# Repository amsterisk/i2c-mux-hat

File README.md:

# I2C Mux HAT

An open-hardware 8-channel I2C multiplexer board for single-board computers with a
Raspberry Pi-compatible 40-pin header (Raspberry Pi, Orange Pi, Banana Pi, ...).

Status: **work in progress** — schematic done (ERC clean), PCB routed (DRC clean), not yet reviewed or fabricated.

## Features

- **TCA9548A** 8-channel I2C switch, address 0x70–0x77 (3-way DIP switch, default 0x70).
- **Per-channel voltage**: a 3-pin jumper selects 3.3 V or 5 V for that channel's pull-ups
  and connector power. The mux runs at 3.3 V and translates levels, so 5 V devices never
  reach the host's GPIO.
- **Per-channel connector**: keyed JST XH 4-pin (B4B-XH-A, vertical).
- 2.2 kΩ pull-ups per channel (enabled by a shunt on a 2-pin header), suitable for a few metres of cable.
- Per-channel resettable fuse on connector power and ESD clamp (USBLC6-2SC6) on SDA/SCL/V.
- Optional mux reset from GPIO4 (2-pin header).
- HAT form factor, 65 × 56.5 mm (no ID EEPROM; pins 27/28 unused).
- **2×20 stacking header**: all 40 pins pass through to another board above.

Example use: DDC/CI control of monitors (input switching, brightness) over HDMI's DDC lines,
with one channel per monitor — every monitor answers on the same addresses (0x37/0x50), so
each needs its own bus.

## Connector pinout

JST XH (J*x*01), Grove pin order:

| Pin | Signal |
|---|---|
| 1 | SCL |
| 2 | SDA |
| 3 | V (3.3 or 5 V, per channel jumper) |
| 4 | GND |

### JST XH → HDMI (DDC) cable

| XH pin | HDMI pin |
|---|---|
| 1 SCL | 15 |
| 2 SDA | 16 |
| 3 V | 18 (+5 V) |
| 4 GND | 17 (bridge to 20 / shell) |

Set that channel to **5 V**. Leave all other HDMI pins unconnected.

## Jumpers

| Ref | Default | Function |
|---|---|---|
| JPx01 (1×3 header) | no shunt | Channel x voltage: 1-2 = 3.3 V, 2-3 = 5 V, none = off |
| JPx02 (1×2 header) | shunt fitted | Channel x pull-ups; remove the shunt to disable |
| JP1 (1×2 header) | open | Fit a shunt to connect mux ~RESET to GPIO4 (pin 7) |
| SW1 (DIP-3, 1.27 mm) | all OFF | Address A0–A2; ON = 1, so 0x70 + A (0x70–0x77) |

All jumpers are 2.54 mm pin headers taking standard shunts.

## Stacking

J1 is a 2×20 stacking header (female, long pins through the board), so every GPIO passes
through. A board above can share I2C (pins 3/5) as long as it avoids addresses 0x70–0x77
(or move this board's address with SW1); GPIO4 is only used if JP1 is bridged; pins
27/28 are free for the upper board's ID EEPROM. Mechanically, the vertical XH plugs and
their cables exit upwards, so a board above needs a tall spacer (about 20 mm or more);
otherwise put this board at the top of the stack.

## Software

The board appears as one I2C device (0x70) on the host's bus on pins 3/5.

- **Raspberry Pi OS**: `dtoverlay=i2c-mux,pca9548,addr=0x70` in `config.txt` gives one
  `/dev/i2c-N` per channel. Keep the bus at ≤100 kHz for long cables / DDC
  (`dtparam=i2c_baudrate=100000`); the TCA9548A is rated to 400 kHz.
- **Other boards**: use a device-tree overlay for `i2c-mux-pca954x`, or select channels
  from userspace by writing the channel bitmask to 0x70 before each transaction.

## Building fabrication files

```sh
tools/export.sh            # version from `git describe`; refuses to build if ERC/DRC fail
tools/export.sh v0.1       # explicit version
tools/export.sh --allow-violations   # work-in-progress builds
```

Outputs land in `production/<version>/` (git-ignored; attach to a GitHub release):
Gerber + drill zip (upload as-is to JLCPCB/PCBWay; the stencil is made from `F.Paste`),
grouped BOM, JLCPCB-format BOM + placement file, schematic PDF, top/bottom 3D renders,
and the ERC/DRC reports. Needs KiCad 9 (`kicad-cli`, or `kicad.kicad-cli` from the snap).

Design rules target JLCPCB's standard 2-layer process (Board Setup → Constraints, plus
`hardware/i2c-mux-hat.kicad_dru`): 0.15 mm track/clearance minimum, 0.6/0.3 mm vias,
0.3 mm copper-to-edge. Net classes: *Default* 0.25 mm tracks; *Power* 0.5 mm for
+5V, +3.3V, GND and each channel's VCH/VOUT/VPU.

## Repository layout

- `hardware/` — KiCad 9 project (`i2c-mux-hat.kicad_pro`); the 8 channels are one hierarchical
  sheet (`channel.kicad_sch`) instanced 8 times.
- `tools/export.sh` — builds fabrication and documentation outputs.
- `LICENSE` — CERN-OHL-S-2.0.

## Licence

Copyright the contributors. Licensed under the **CERN Open Hardware Licence Version 2 –
Strongly Reciprocal** (CERN-OHL-S-2.0). See `LICENSE`.

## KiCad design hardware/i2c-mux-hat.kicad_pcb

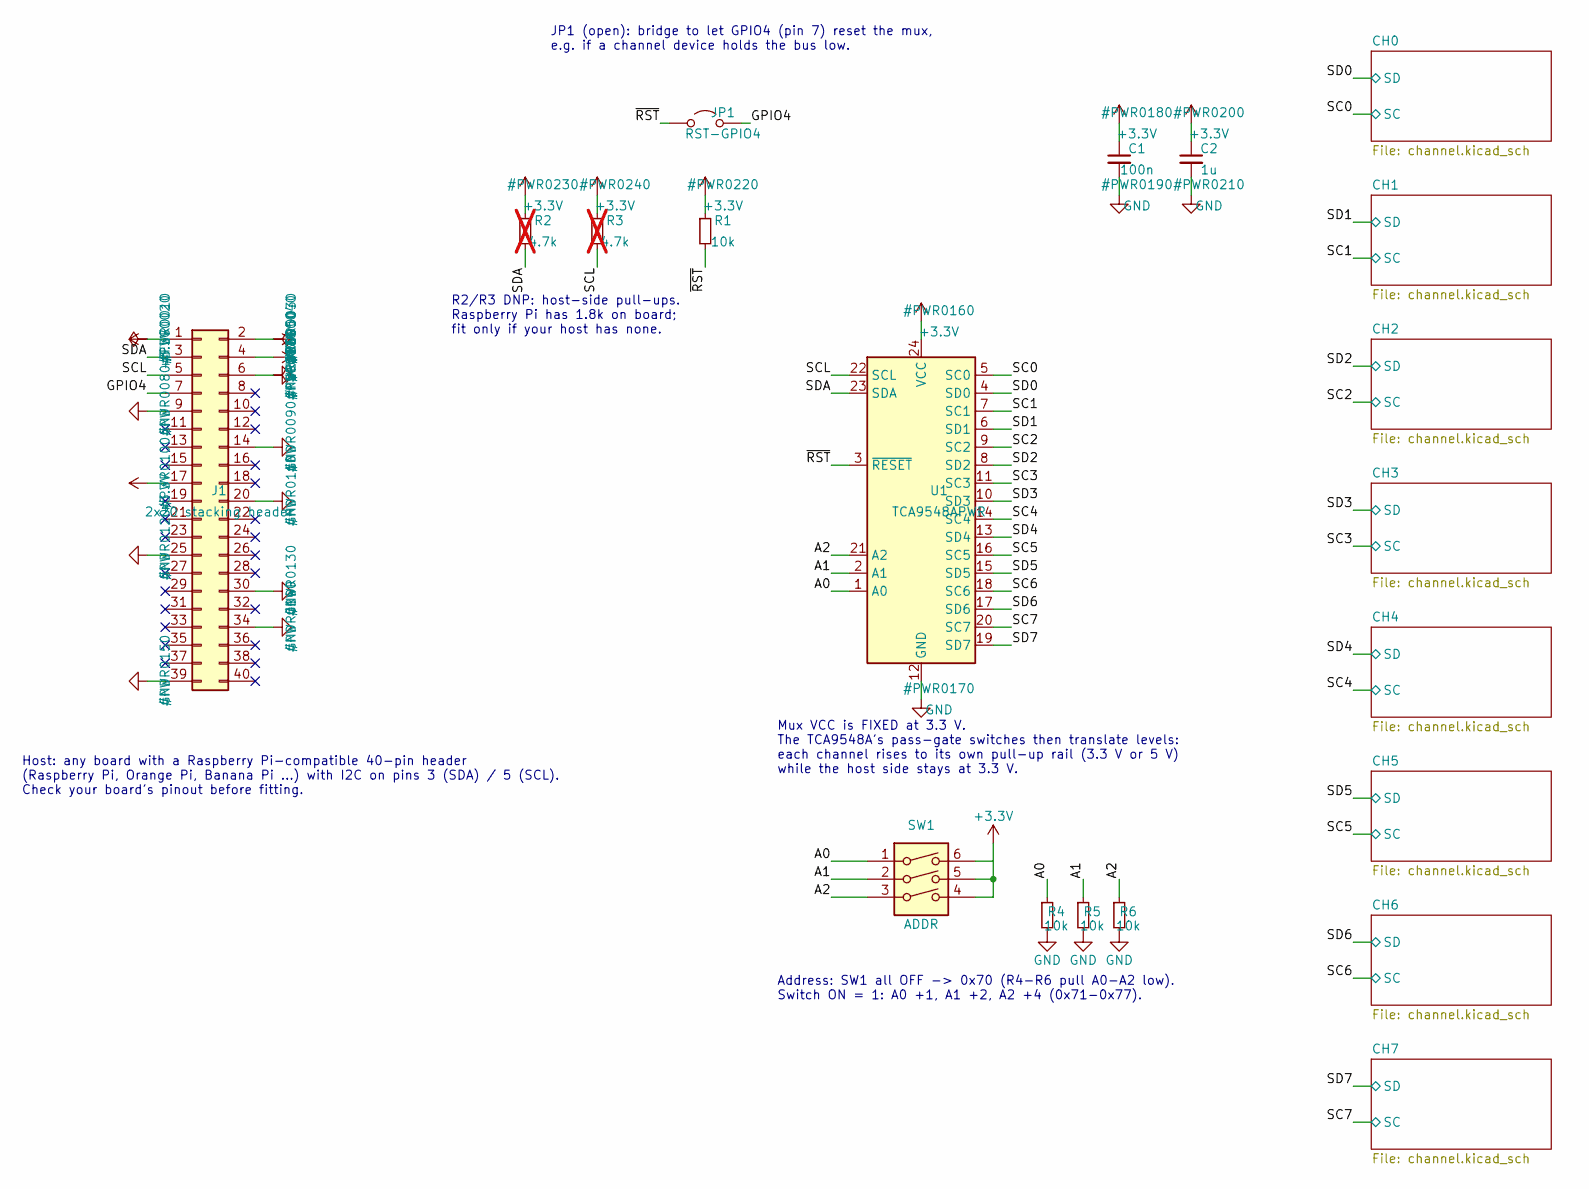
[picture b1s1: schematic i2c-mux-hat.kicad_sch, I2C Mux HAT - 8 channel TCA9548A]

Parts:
C1: 100n; C_0603_1608Metric
C2: 1u; C_0603_1608Metric
J1: 2x20 stacking header; PinSocket_2x20_P2.54mm_Vertical
JP1: RST-GPIO4; PinHeader_1x02_P2.54mm_Vertical
R1, R4, R5, R6: 10k; R_0603_1608Metric
R2, R3: 4.7k; R_0603_1608Metric; not fitted
SW1: ADDR; SW_DIP_SPSTx03_Slide_KingTek_DSHP03TS_W7.62mm_P1.27mm
U1: TCA9548APWR; TSSOP-24_4.4x7.8mm_P0.65mm

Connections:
+3.3V: C1.1, C2.1, J1.1, J1.17, R1.1, R2.1, R3.1, SW1.4, SW1.5, SW1.6, U1.24 (VCC); also elsewhere on the board
+5V: J1.2, J1.4; also elsewhere on the board
/A0: R4.1, SW1.1, U1.1 (A0)
/A1: R5.1, SW1.2, U1.2 (A1)
/A2: R6.1, SW1.3, U1.21 (A2)
/GPIO4: J1.7, JP1.2 (B)
/SC0: U1.5 (SC0); also elsewhere on the board
/SC1: U1.7 (SC1); also elsewhere on the board
/SC2: U1.9 (SC2); also elsewhere on the board
/SC3: U1.11 (SC3); also elsewhere on the board
/SC4: U1.14 (SC4); also elsewhere on the board
/SC5: U1.16 (SC5); also elsewhere on the board
/SC6: U1.18 (SC6); also elsewhere on the board
/SC7: U1.20 (SC7); also elsewhere on the board
/SCL: J1.5, R3.2, U1.22 (SCL)
/SD0: U1.4 (SD0); also elsewhere on the board
/SD1: U1.6 (SD1); also elsewhere on the board
/SD2: U1.8 (SD2); also elsewhere on the board
/SD3: U1.10 (SD3); also elsewhere on the board
/SD4: U1.13 (SD4); also elsewhere on the board
/SD5: U1.15 (SD5); also elsewhere on the board
/SD6: U1.17 (SD6); also elsewhere on the board
/SD7: U1.19 (SD7); also elsewhere on the board
/SDA: J1.3, R2.2, U1.23 (SDA)
/~RST: JP1.1 (A), R1.2, U1.3 (~RESET)
GND: C1.2, C2.2, J1.6, J1.9, J1.14, J1.20, J1.25, J1.30, J1.34, J1.39, R4.2, R5.2, R6.2, U1.12 (GND); also elsewhere on the board

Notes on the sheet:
Address: SW1 all OFF -> 0x70 (R4-R6 pull A0-A2 low). Switch ON = 1: A0 +1, A1 +2, A2 +4 (0x71-0x77).
JP1 (open): bridge to let GPIO4 (pin 7) reset the mux, e.g. if a channel device holds the bus low.
R2/R3 DNP: host-side pull-ups. Raspberry Pi has 1.8k on board; fit only if your host has none.
Host: any board with a Raspberry Pi-compatible 40-pin header (Raspberry Pi, Orange Pi, Banana Pi ...) with I2C on pins 3 (SDA) / 5 (SCL). Check your board's pinout before fitting.
Mux VCC is FIXED at 3.3 V. The TCA9548A's pass-gate switches then translate levels: each channel rises to its own pull-up rail (3.3 V or 5 V) while the host side stays at 3.3 V.

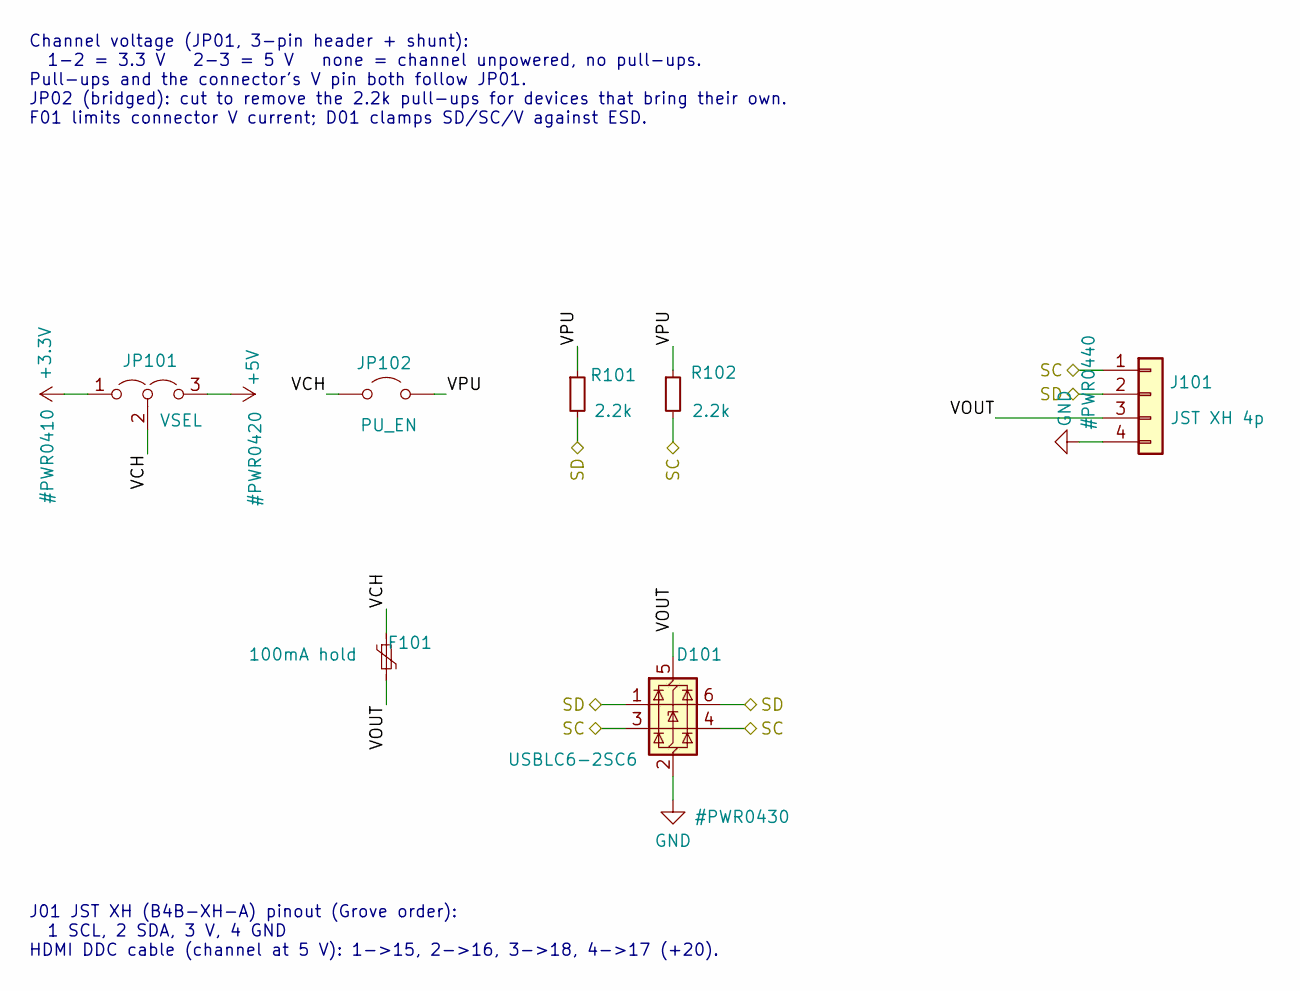
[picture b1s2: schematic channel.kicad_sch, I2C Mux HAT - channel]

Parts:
D101: USBLC6-2SC6; SOT-23-6
F101: 100mA hold; Fuse_0805_2012Metric
J101: JST XH 4p; JST_XH_B4B-XH-A_1x04_P2.50mm_Vertical
JP101: VSEL; PinHeader_1x03_P2.54mm_Vertical
JP102: PU_EN; PinHeader_1x02_P2.54mm_Vertical
R101, R102: 2.2k; R_0603_1608Metric

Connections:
+3.3V: JP101.1 (A); also elsewhere on the board
+5V: JP101.3 (B); also elsewhere on the board
/CH0/VCH: F101.1, JP101.2 (C), JP102.1 (A)
/CH0/VOUT: D101.5 (VBUS), F101.2, J101.3
/CH0/VPU: JP102.2 (B), R101.1, R102.1
/SC0: D101.3 (I/O2), D101.4 (I/O2), J101.1, R102.2; also elsewhere on the board
/SD0: D101.1 (I/O1), D101.6 (I/O1), J101.2, R101.2; also elsewhere on the board
GND: D101.2 (GND), J101.4; also elsewhere on the board

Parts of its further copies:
D201, D301, D401, D501, D601, D701, D801: USBLC6-2SC6; SOT-23-6
F201, F301, F401, F501, F601, F701, F801: 100mA hold; Fuse_0805_2012Metric
J201, J301, J401, J501, J601, J701, J801: JST XH 4p; JST_XH_B4B-XH-A_1x04_P2.50mm_Vertical
JP201, JP301, JP401, JP501, JP601, JP701, JP801: VSEL; PinHeader_1x03_P2.54mm_Vertical
JP202, JP302, JP402, JP502, JP602, JP702, JP802: PU_EN; PinHeader_1x02_P2.54mm_Vertical
R201, R202, R301, R302, R401, R402, R501, R502, R601, R602, R701, R702, R801, R802: 2.2k; R_0603_1608Metric

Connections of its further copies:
+3.3V: JP201.1 (A), JP301.1 (A), JP401.1 (A), JP501.1 (A), JP601.1 (A), JP701.1 (A), JP801.1 (A); also elsewhere on the board
+5V: JP201.3 (B), JP301.3 (B), JP401.3 (B), JP501.3 (B), JP601.3 (B), JP701.3 (B), JP801.3 (B); also elsewhere on the board
/CH1/VCH: F201.1, JP201.2 (C), JP202.1 (A)
/CH1/VOUT: D201.5 (VBUS), F201.2, J201.3
/CH1/VPU: JP202.2 (B), R201.1, R202.1
/CH2/VCH: F301.1, JP301.2 (C), JP302.1 (A)
/CH2/VOUT: D301.5 (VBUS), F301.2, J301.3
/CH2/VPU: JP302.2 (B), R301.1, R302.1
/CH3/VCH: F401.1, JP401.2 (C), JP402.1 (A)
/CH3/VOUT: D401.5 (VBUS), F401.2, J401.3
/CH3/VPU: JP402.2 (B), R401.1, R402.1
/CH4/VCH: F501.1, JP501.2 (C), JP502.1 (A)
/CH4/VOUT: D501.5 (VBUS), F501.2, J501.3
/CH4/VPU: JP502.2 (B), R501.1, R502.1
/CH5/VCH: F601.1, JP601.2 (C), JP602.1 (A)
/CH5/VOUT: D601.5 (VBUS), F601.2, J601.3
/CH5/VPU: JP602.2 (B), R601.1, R602.1
/CH6/VCH: F701.1, JP701.2 (C), JP702.1 (A)
/CH6/VOUT: D701.5 (VBUS), F701.2, J701.3
/CH6/VPU: JP702.2 (B), R701.1, R702.1
/CH7/VCH: F801.1, JP801.2 (C), JP802.1 (A)
/CH7/VOUT: D801.5 (VBUS), F801.2, J801.3
/CH7/VPU: JP802.2 (B), R801.1, R802.1
/SC1: D201.3 (I/O2), D201.4 (I/O2), J201.1, R202.2; also elsewhere on the board
/SC2: D301.3 (I/O2), D301.4 (I/O2), J301.1, R302.2; also elsewhere on the board
/SC3: D401.3 (I/O2), D401.4 (I/O2), J401.1, R402.2; also elsewhere on the board
/SC4: D501.3 (I/O2), D501.4 (I/O2), J501.1, R502.2; also elsewhere on the board
/SC5: D601.3 (I/O2), D601.4 (I/O2), J601.1, R602.2; also elsewhere on the board
/SC6: D701.3 (I/O2), D701.4 (I/O2), J701.1, R702.2; also elsewhere on the board
/SC7: D801.3 (I/O2), D801.4 (I/O2), J801.1, R802.2; also elsewhere on the board
/SD1: D201.1 (I/O1), D201.6 (I/O1), J201.2, R201.2; also elsewhere on the board
/SD2: D301.1 (I/O1), D301.6 (I/O1), J301.2, R301.2; also elsewhere on the board
/SD3: D401.1 (I/O1), D401.6 (I/O1), J401.2, R401.2; also elsewhere on the board
/SD4: D501.1 (I/O1), D501.6 (I/O1), J501.2, R501.2; also elsewhere on the board
/SD5: D601.1 (I/O1), D601.6 (I/O1), J601.2, R601.2; also elsewhere on the board
/SD6: D701.1 (I/O1), D701.6 (I/O1), J701.2, R701.2; also elsewhere on the board
/SD7: D801.1 (I/O1), D801.6 (I/O1), J801.2, R801.2; also elsewhere on the board
GND: D201.2 (GND), D301.2 (GND), D401.2 (GND), D501.2 (GND), D601.2 (GND), D701.2 (GND), D801.2 (GND), J201.4, J301.4, J401.4, J501.4, J601.4, J701.4, J801.4; also elsewhere on the board

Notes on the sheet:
J01 JST XH (B4B-XH-A) pinout (Grove order): 1 SCL, 2 SDA, 3 V, 4 GND HDMI DDC cable (channel at 5 V): 1->15, 2->16, 3->18, 4->17 (+20).
Channel voltage (JP01, 3-pin header + shunt): 1-2 = 3.3 V 2-3 = 5 V none = channel unpowered, no pull-ups. Pull-ups and the connector's V pin both follow JP01. JP02 (bridged): cut to remove the 2.2k pull-ups for devices that bring their own. F01 limits connector V current; D01 clamps SD/SC/V agains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

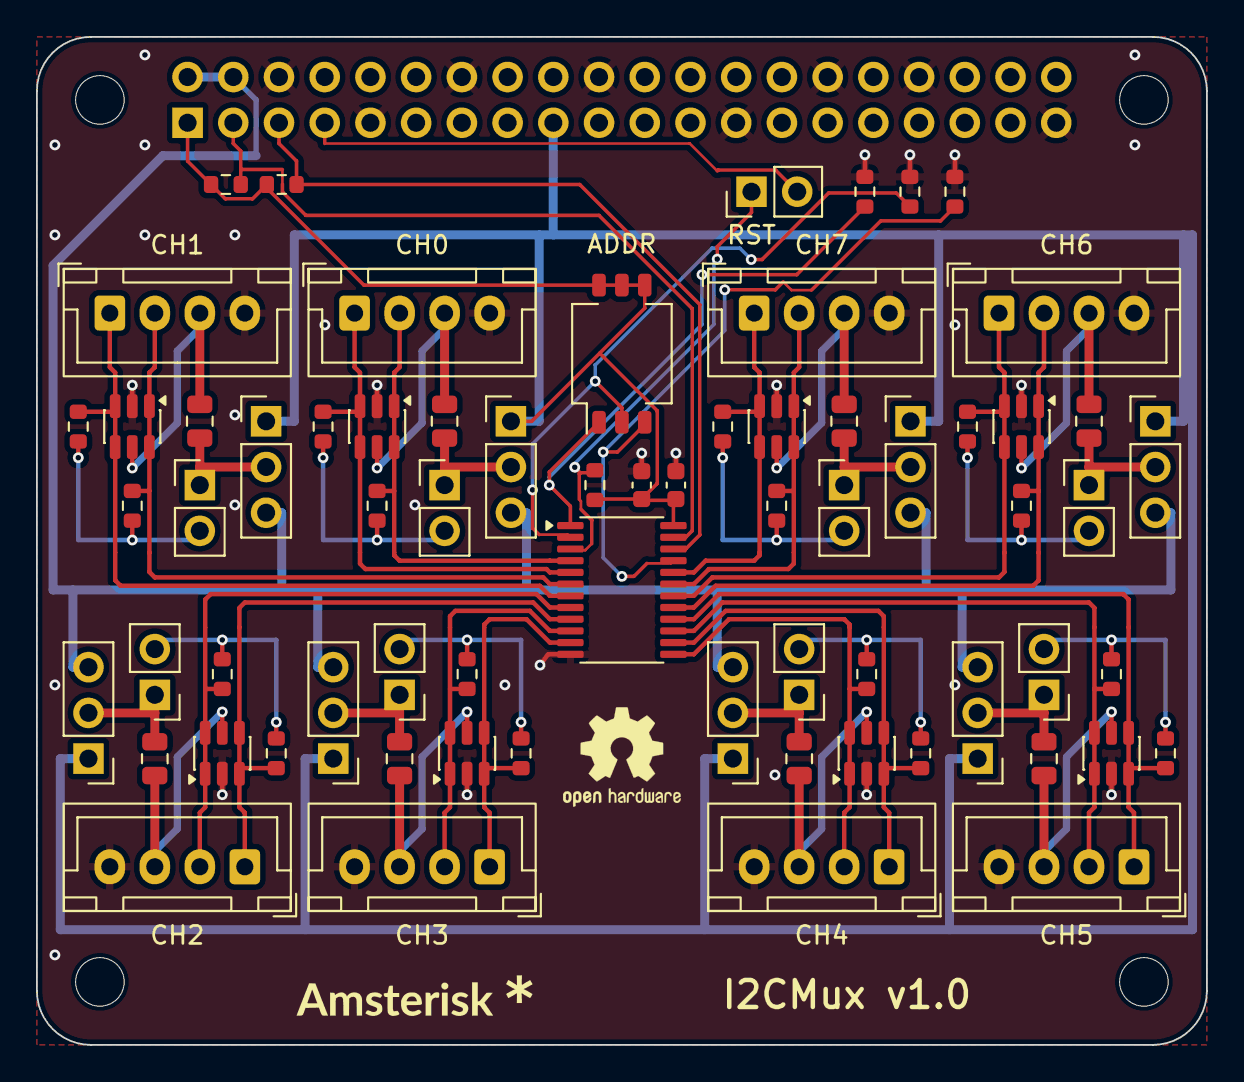
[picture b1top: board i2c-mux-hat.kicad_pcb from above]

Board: 2 copper layers, 65.0 x 56.0 mm, 74 parts (1 on the bottom side), 50 nets.

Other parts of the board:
LOGO1: LOGO; image-small
LOGO2: OSHW-Logo2_7.3x6mm_SilkScreen
MH1, MH2, MH3, MH4: MountingHole_2.7mm_M2.5

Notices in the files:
hardware/i2c-mux-hat.kicad_pcb:
I2CMux v1.0 CERN-OHL-S-2.0
